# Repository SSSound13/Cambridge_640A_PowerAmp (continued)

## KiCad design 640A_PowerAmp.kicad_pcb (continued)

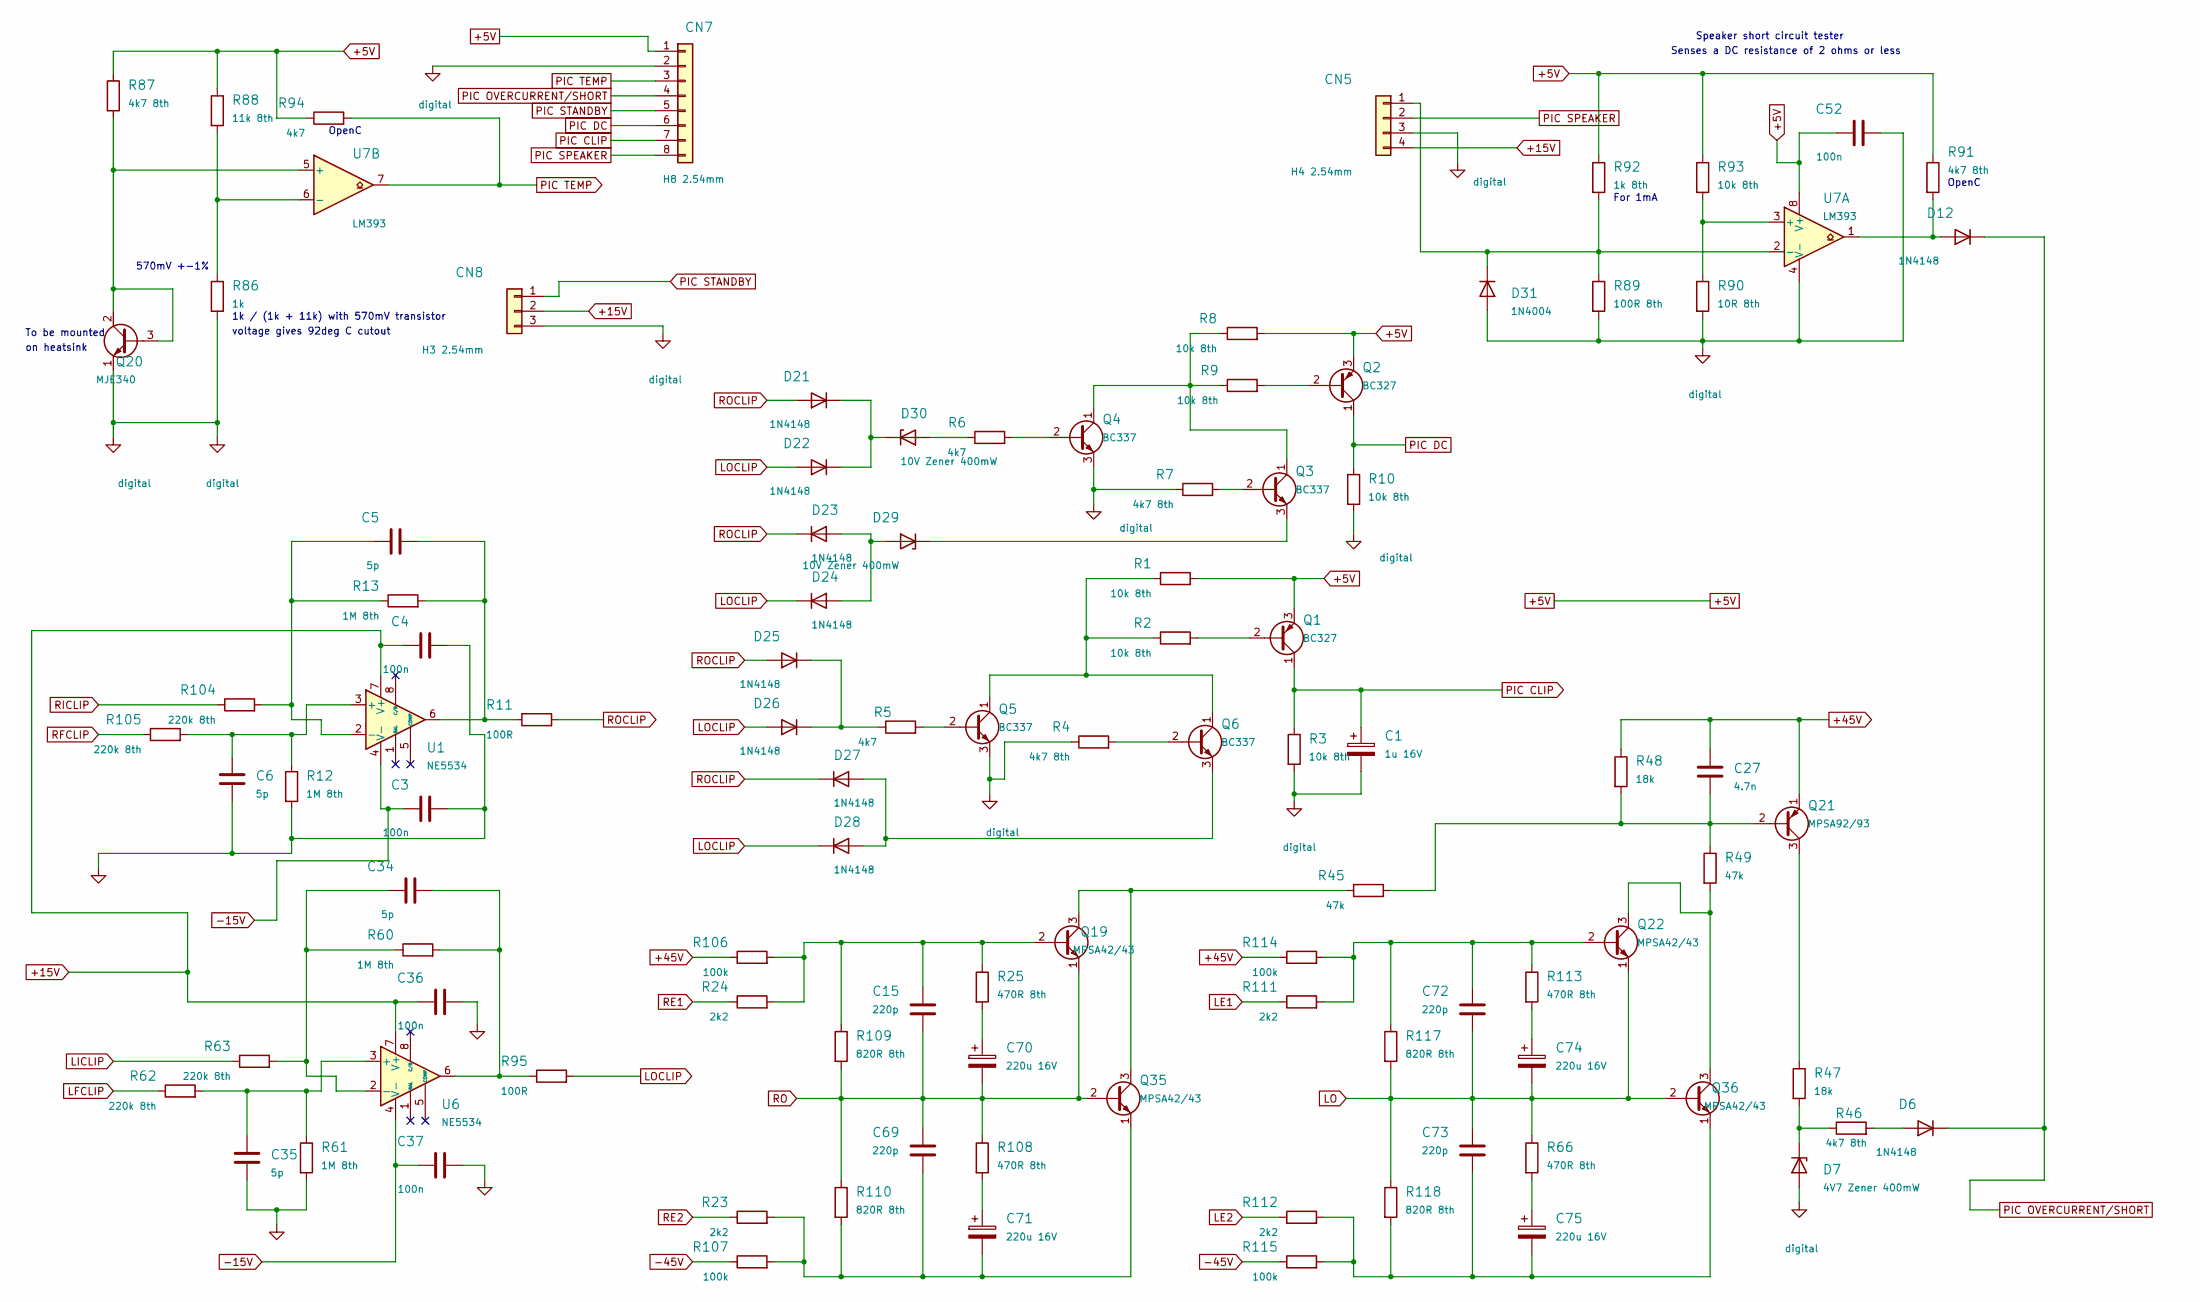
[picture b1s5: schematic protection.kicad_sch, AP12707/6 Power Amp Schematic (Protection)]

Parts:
C1: 1u 16V; CP_Radial_D5.0mm_P2.50mm
C3, C4, C36, C37, C52: 100n; C_Disc_D7.5mm_W2.5mm_P5.00mm
C5, C6, C34, C35: 5p; C_Disc_D5.0mm_W2.5mm_P5.00mm
C15, C69, C72, C73: 220p; C_Disc_D5.0mm_W2.5mm_P5.00mm
C27: 4.7n; C_Disc_D7.5mm_W2.5mm_P5.00mm
C70, C71, C74, C75: 220u 16V; CP_Radial_D5.0mm_P2.50mm
CN5: H4 2.54mm; JST_XH_B4B-XH-A_1x04_P2.50mm_Vertical
CN7: H8 2.54mm; JST_XH_B8B-XH-A_1x08_P2.50mm_Vertical
CN8: H3 2.54mm; JST_XH_B3B-XH-A_1x03_P2.50mm_Vertical
D6, D12, D21, D22, D23, D24, D25, D26, D27, D28: 1N4148; D_DO-35_SOD27_P7.62mm_Horizontal
D7: 4V7 Zener 400mW; D_DO-35_SOD27_P7.62mm_Horizontal
D29, D30: 10V Zener 400mW; D_DO-35_SOD27_P7.62mm_Horizontal
D31: 1N4004; D_DO-41_SOD81_P10.16mm_Horizontal
Q1, Q2: BC327; TO-92_Inline_Wide
Q3, Q4, Q5, Q6: BC337; TO-92_Inline_Wide
Q19, Q22, Q35, Q36: MPSA42/43; TO-92_Inline_Wide
Q20: MJE340; TO-126-3_Vertical
Q21: MPSA92/93; TO-92_Inline_Wide
R1, R2, R3, R8, R9, R10, R93: 10k 8th; R_Axial_DIN0204_L3.6mm_D1.6mm_P7.62mm_Horizontal
R4, R7, R87, R91: 4k7 8th; R_Axial_DIN0204_L3.6mm_D1.6mm_P7.62mm_Horizontal
R5, R6, R94: 4k7; R_Axial_DIN0207_L6.3mm_D2.5mm_P10.16mm_Horizontal
R11, R95: 100R; R_Axial_DIN0207_L6.3mm_D2.5mm_P10.16mm_Horizontal
R12, R13, R60, R61: 1M 8th; R_Axial_DIN0204_L3.6mm_D1.6mm_P7.62mm_Horizontal
R23, R24, R111, R112: 2k2; R_Axial_DIN0207_L6.3mm_D2.5mm_P10.16mm_Horizontal
R25, R66, R108, R113: 470R 8th; R_Axial_DIN0204_L3.6mm_D1.6mm_P7.62mm_Horizontal
R45, R49: 47k; R_Axial_DIN0207_L6.3mm_D2.5mm_P10.16mm_Horizontal
R46: 4k7 8th; R_Axial_DIN0207_L6.3mm_D2.5mm_P10.16mm_Horizontal
R47, R48: 18k; R_Axial_DIN0207_L6.3mm_D2.5mm_P10.16mm_Horizontal
R62, R63, R104, R105: 220k 8th; R_Axial_DIN0204_L3.6mm_D1.6mm_P7.62mm_Horizontal
R86: 1k; R_Axial_DIN0207_L6.3mm_D2.5mm_P10.16mm_Horizontal
R88: 11k 8th; R_Axial_DIN0204_L3.6mm_D1.6mm_P7.62mm_Horizontal
R89: 100R 8th; R_Axial_DIN0204_L3.6mm_D1.6mm_P7.62mm_Horizontal
R90: 10R 8th; R_Axial_DIN0204_L3.6mm_D1.6mm_P7.62mm_Horizontal
R92: 1k 8th; R_Axial_DIN0204_L3.6mm_D1.6mm_P7.62mm_Horizontal
R106, R107, R114, R115: 100k; R_Axial_DIN0207_L6.3mm_D2.5mm_P10.16mm_Horizontal
R109, R110, R117, R118: 820R 8th; R_Axial_DIN0204_L3.6mm_D1.6mm_P7.62mm_Horizontal
U1, U6: NE5534; DIP-8_W7.62mm
U7: LM393; DIP-8_W7.62mm

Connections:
+5V: C52.1, CN7.1, Q1.3 (E), Q2.3 (E), R1.2, R8.2, R87.1, R88.1, R91.1, R92.1, R93.1, R94.1, U7.8 (V+); also elsewhere on the board
+15V: C4.1, C36.1, CN5.4, CN8.2, U1.7 (V+), U6.7 (V+); also elsewhere on the board
+45V: C27.1, Q21.1 (E), R48.1, R106.1, R114.1; also elsewhere on the board
-15V: C3.1, C37.1, U1.4 (V-), U6.4 (V-); also elsewhere on the board
-45V: R107.1, R115.1; also elsewhere on the board
GND: C3.2, C4.2, C6.2, C35.2, C36.2, C37.2, R12.2, R61.2; also elsewhere on the board
LE1: R111.1; also elsewhere on the board
LE2: R112.1; also elsewhere on the board
LFCLIP: R62.1; also elsewhere on the board
LICLIP: R63.1; also elsewhere on the board
LO: C72.2, C73.1, C74.2, Q22.1 (E), Q36.2 (B), R66.1, R117.2, R118.1; also elsewhere on the board
LOCLIP: D22.2 (A), D24.1 (K), D26.2 (A), D28.1 (K), R95.2
unnamed: C5.2, R11.1, R13.2, U1.6
unnamed: C34.2, R60.2, R95.1, U6.6
unnamed: C70.1, R25.2
unnamed: C71.1, R108.2
unnamed: C74.1, R113.2
unnamed: C75.1, R66.2
unnamed: CN5.1, D31.1 (K), R89.1, R92.2, U7.2 (-)
unnamed: D6.2 (A), R46.2
unnamed: D7.1 (K), R46.1, R47.2
unnamed: D12.2 (A), R91.2, U7.1
unnamed: D21.1 (K), D22.1 (K), D30.1 (K)
unnamed: D23.2 (A), D24.2 (A), D29.2 (A)
unnamed: D25.1 (K), D26.1 (K), R5.1
unnamed: D27.2 (A), D28.2 (A), Q6.3 (E)
unnamed: D29.1 (K), Q3.3 (E)
unnamed: D30.2 (A), R6.1
unnamed: Q1.2 (B), R2.2
unnamed: Q2.2 (B), R9.2
unnamed: Q3.2 (B), R7.2
unnamed: Q3.1 (C), Q4.1 (C), R8.1, R9.1
unnamed: Q4.2 (B), R6.2
unnamed: Q5.2 (B), R5.2
unnamed: Q5.1 (C), Q6.1 (C), R1.1, R2.1
unnamed: Q6.2 (B), R4.2
unnamed: C15.1, Q19.2 (B), R24.2, R25.1, R106.2, R109.1
unnamed: Q19.3 (C), Q35.3 (C), R45.1
unnamed: Q20.2 (C), Q20.3 (B), R87.2, U7.5 (+)
unnamed: C27.2, Q21.2 (B), R45.2, R48.2, R49.1
unnamed: Q21.3 (C), R47.1
unnamed: C72.1, Q22.2 (B), R111.2, R113.1, R114.2, R117.1
unnamed: Q22.3 (C), Q36.3 (C), R49.2
unnamed: C69.2, C71.2, Q35.1 (E), R23.2, R107.2, R110.2
unnamed: C73.2, C75.2, Q36.1 (E), R112.2, R115.2, R118.2
unnamed: C6.1, R12.1, R105.2, U1.3 (+)
unnamed: C5.1, R13.1, R104.2, U1.2 (-)
unnamed: C35.1, R61.1, R62.2, U6.3 (+)
unnamed: C34.1, R60.1, R63.2, U6.2 (-)
unnamed: R90.1, R93.2, U7.3 (+)
unnamed: R86.1, R88.2, U7.6 (-)
PIC CLIP: C1.1, CN7.7, Q1.1 (C), R3.1
PIC DC: CN7.6, Q2.1 (C), R10.1
PIC OVERCURRENT/SHORT: CN7.4, D6.1 (K), D12.1 (K)
PIC SPEAKER: CN5.2, CN7.8
PIC STANDBY: CN7.5, CN8.1
PIC TEMP: CN7.3, R94.2, U7.7
RE1: R24.1; also elsewhere on the board
RE2: R23.1; also elsewhere on the board
RFCLIP: R105.1; also elsewhere on the board
RICLIP: R104.1; also elsewhere on the board
RO: C15.2, C69.1, C70.2, Q19.1 (E), Q35.2 (B), R108.1, R109.2, R110.1; also elsewhere on the board
ROCLIP: D21.2 (A), D23.1 (K), D25.2 (A), D27.1 (K), R11.2
digital: C1.2, C52.2, CN5.3, CN7.2, CN8.3, D7.2 (A), D31.2 (A), Q4.3 (E), Q5.3 (E), Q20.1 (E), R3.2, R4.1, R7.1, R10.2, R86.2, R89.2, R90.2, U7.4 (V-); also elsewhere on the board

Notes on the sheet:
570mV +-1%
For 1mA
OpenC
Senses a DC resistance of 2 ohms or less
To be mounted
Speaker short circuit tester
on heatsink
voltage gives 92deg C cutout
1k / (1k + 11k) with 570mV transistor

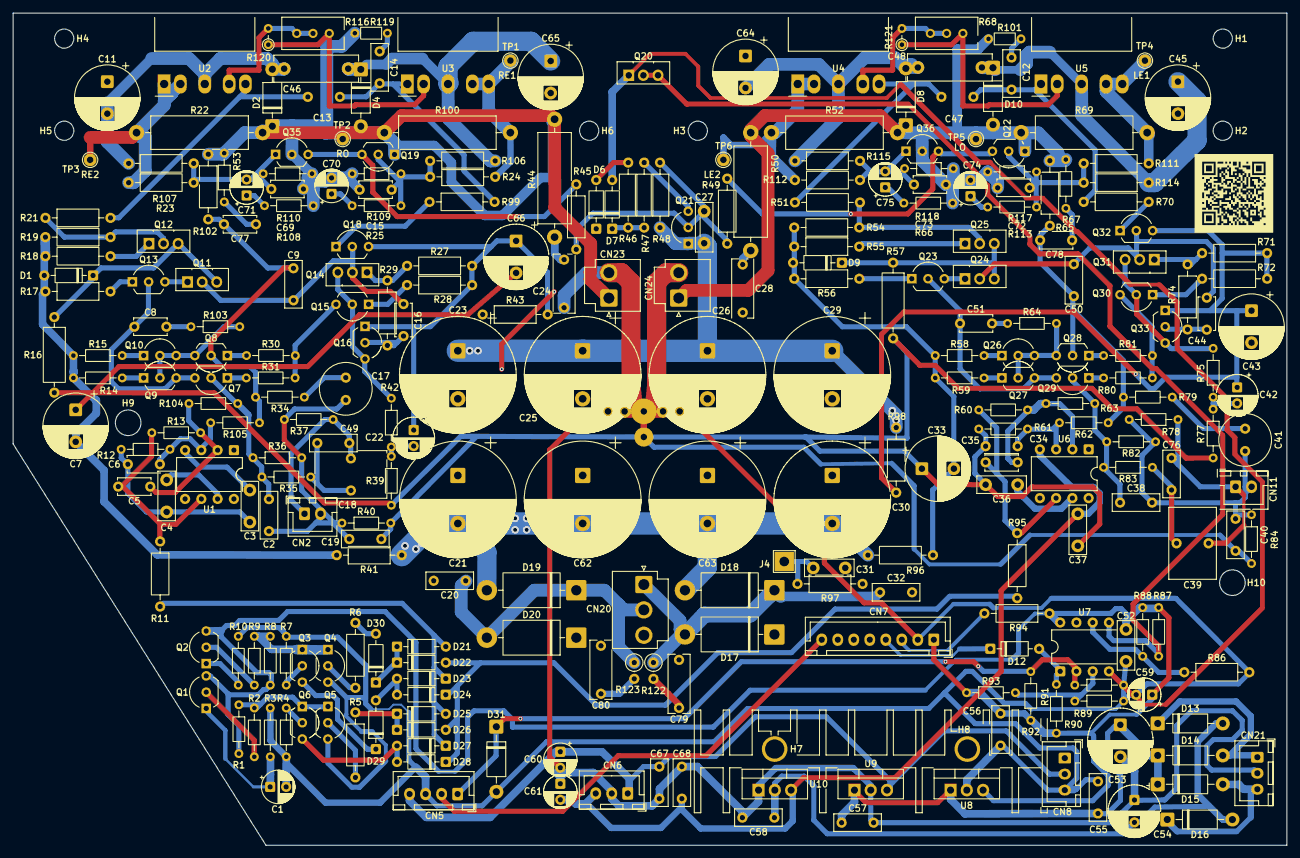
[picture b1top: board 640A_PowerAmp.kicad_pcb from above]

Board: 4 copper layers, 198.9 x 130.0 mm, 296 parts (0 on the bottom side), 141 nets.

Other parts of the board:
H1, H2, H3, H4, H5, H6: bracket fixing, 3.0 mm NPTH; MountingHole_NPTH_3.0mm
H7: heatsink pin, 3.0 mm PTH; MountingHole_PTH_3.0mm_Pad4.0mm
H8: heatsink pin, 3.0 mm PTH; no separate digital tra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; MountingHole_PTH_3.0mm_Pad4.0mm
H9, H10: standoff, 4.0 mm NPTH; MountingHole_NPTH_4.0mm

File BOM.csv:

Группа;Кол-во;Обозначения;Номинал;Корпус;Производитель и партномер;Новое/заменено;Не устанавливать;Код ЧИП и ДИП;Примечание
Резисторы;11;R1, R2, R3, R8, R9, R10, R39, R42, R75, R77, R93;10k, 0,125 Вт;DIN0204, шаг 7,62;;;;;
Резисторы;6;R4, R7, R35, R83, R87, R91;4k7, 0,125 Вт;DIN0204, шаг 7,62;;;;;
Резисторы;3;R5, R6, R94;4k7;DIN0207, шаг 10,16;;;;;
Резисторы;8;R11, R17, R21, R51, R56, R70, R95, R99;100R;DIN0207, шаг 10,16;;;;;
Резисторы;4;R12, R13, R60, R61;1M, 0,125 Вт;DIN0204, шаг 7,62;;;;;
Резисторы;4;R14, R15, R58, R59;47R, 0,125 Вт;DIN0204, шаг 7,62;;;;;
Резисторы;2;R16, R57;8k2 0,66 Вт;DIN0309, шаг 11,81;;;;;
Резисторы;5;R18, R29, R55, R74, R86;1k;DIN0207, шаг 10,16;;;;;
Резисторы;4;R19, R47, R48, R54;18k;DIN0207, шаг 10,16;;;;;
Резисторы;4;R22, R52, R69, R100;0.22R 3 Вт;DIN0516, шаг 19,69;;;;;
Резисторы;4;R23, R24, R111, R112;2k2;DIN0207, шаг 10,16;;;;;
Резисторы;4;R25, R66, R108, R113;470R, 0,125 Вт;DIN0204, шаг 7,62;;;;;
Резисторы;4;R27, R28, R71, R72;150R;DIN0207, шаг 10,16;;;;;
Резисторы;5;R30, R31, R80, R81, R89;100R, 0,125 Вт;DIN0204, шаг 7,62;;;;;
Резисторы;3;R34, R79, R92;1k, 0,125 Вт;DIN0204, шаг 7,62;;;;;
Резисторы;2;R36, R82;33k, 0,125 Вт;DIN0204, шаг 7,62;;;;;
Резисторы;2;R37, R78;330k, 0,125 Вт;DIN0204, шаг 7,62;;;;;
Резисторы;3;R40, R84, R90;10R, 0,125 Вт;DIN0204, шаг 7,62;;;;;
Резисторы;4;R41, R43, R96, R98;150R 0,5 Вт fusible;DIN0207, шаг 10,16;TE Connectivity (Neohm) FRN50J150R/S;да;;8003870514;
Резисторы;2;R44, R50;4R7 3 Вт wirewound;DIN0516, шаг 18,42;Vishay AC03000004708JAC00;да;;8017149996;"ставить на выводах ~3 мм над платой (иначе касается R45); можно родные со старой платы"
Резисторы;2;R45, R49;47k;DIN0207, шаг 10,16;;;;;
Резисторы;1;R46;4k7, 0,125 Вт;DIN0207, шаг 10,16;;;;;
Резисторы;1;R53;150R, 0,125 Вт;DIN0204, шаг 7,62;;;;;
Резисторы;4;R62, R63, R104, R105;220k, 0,125 Вт;DIN0204, шаг 7,62;;;;;
Резисторы;3;R64, R67, R103;150R;DIN0204, шаг 7,62;;;;;
Резисторы;2;R65, R102;33k;DIN0207, шаг 10,16;;;;;
Резисторы;2;R68, R116;47R;Bourns 3296W;;;;;подстроечник тока покоя
Резисторы;1;R88;11k, 0,125 Вт;DIN0204, шаг 7,62;;;;;
Резисторы;1;R97;47R;DIN0207, шаг 10,16;;;;;
Резисторы;2;R101, R119;47R, 0,125 Вт;DIN0204, шаг 5,08;;;;;
Резисторы;4;R106, R107, R114, R115;100k;DIN0207, шаг 10,16;;;;;
Резисторы;4;R109, R110, R117, R118;820R, 0,125 Вт;DIN0204, шаг 7,62;;;;;
Резисторы;2;R120, R121;100R 1%;DIN0204 вертикально;MF-25 0.25W 100R 1%;да;;47324;
Резисторы;2;R122, R123;47R 0,5 Вт MO;DIN0207 вертикально;MO-50 0.5W 47R 5%;да;;9000040018;номинал подобрать по звону вторички
Конденсаторы;1;C1;1u 16V;радиальный Ø5, шаг 2,5;;;;;
Конденсаторы;2;C2, C38;100p poly;7,2×2,5 мм, шаг 5;;;;;
Конденсаторы;6;C3, C4, C31, C36, C37, C52;100n;диск Ø7,5, шаг 5;;;;;
Конденсаторы;4;C5, C6, C34, C35;5p;диск Ø5, шаг 5;;;;;
Конденсаторы;8;C7, C11, C33, C43, C45, C64, C65, C66;220u 50V;радиальный Ø10, шаг 5;;;;;C7/C33/C43/C66 желательно на 63 В
Конденсаторы;2;C8, C51;470p;диск Ø5, шаг 5;;;;;
Конденсаторы;2;C9, C50;33p;7,2×2,5 мм, шаг 5;;;;;
Конденсаторы;2;C12, C14;15n poly;7,2×2,5 мм, шаг 5;;;;;
Конденсаторы;2;C13, C47;10u NP 16V;радиальный Ø5, шаг 5;;;;;
Конденсаторы;4;C15, C69, C72, C73;220p;диск Ø5, шаг 5;;;;;
Конденсаторы;2;C16, C44;5p;диск Ø5, шаг 5;;;да;;**не устанавливать** (DNP), место под коррекцию на случай возбуждения
Конденсаторы;2;C17, C41;220u NP 10V (D8);радиальный Ø8, шаг 3,5;Panasonic ECE-A1AN221U;да;;8072492276;
Конденсаторы;2;C18, C39;2u2 100V film (MKS2);7,2×11 мм, шаг 5;WIMA MKS2D042201N00KO00 (MKS2-2.2U/100-R);да;;9000788913;
Конденсаторы;10;C19, C20, C32, C40, C55, C56, C57, C58, C67, C68;47n poly;7,2×2,5 мм, шаг 5;;;;;
Конденсаторы;8;C21, C23, C25, C26, C29, C30, C62, C63;2200uF;радиальный Ø18, шаг 7,5;;;;;
Конденсаторы;2;C22, C42;47u 50V;радиальный Ø6,3, шаг 2,5;;;;;C22 брать Ø5 мм — место тесное
Конденсаторы;4;C24, C28, C79, C80;100n 250V MKT;9×3,2 мм, шаг 7,5;TDK (EPCOS) B32560J3104K000;да;;8002013680;
Конденсаторы;1;C27;4.7n;диск Ø7,5, шаг 5;;;;;
Конденсаторы;2;C46, C48;100n 160V Poly;13×4 мм, шаг 10;;;;;
Конденсаторы;2;C49, C76;2.2n PPE Bypass (640A only);7,2×2,5 мм, шаг 5;;;;;
Конденсаторы;1;C53;470u 35V;радиальный Ø10, шаг 5;;;;;
Конденсаторы;1;C54;100u 35V;радиальный Ø8, шаг 3,5;;;;;
Конденсаторы;1;C59;47u 16V;радиальный Ø5, шаг 2,5;;;;;
Конденсаторы;2;C60, C61;100u 16V;радиальный Ø5, шаг 2,5;;;;;
Конденсаторы;4;C70, C71, C74, C75;220u 16V;радиальный Ø5, шаг 2,5;;;;;
Конденсаторы;2;C77, C78;22p;диск Ø5, шаг 5;;;;;
Диоды;2;D1, D9;ZEN 3V3;DO 35, шаг 7,62;;;;;
Диоды;4;D2, D4, D8, D10;1N4004;DO 41, шаг 8,89;;;;;
Диоды;10;D6, D12, D21, D22, D23, D24, D25, D26, D27, D28;1N4148;DO 35, шаг 7,62;;;;;
Диоды;1;D7;4V7 Zener 400mW;DO 35, шаг 7,62;;;;;
Диоды;5;D13, D14, D15, D16, D31;1N4004;DO 41, шаг 10,16;;;;;
Диоды;4;D17, D18, D19, D20;BY550-400;DO 201AD, шаг 13,97;Diotec BY550-400;да;;8026566344;
Диоды;2;D29, D30;10V Zener 400mW;DO 35, шаг 7,62;;;;;
Транзисторы;2;Q1, Q2;BC327;TO-92;;;;;
Транзисторы;4;Q3, Q4, Q5, Q6;BC337;TO-92;;;;;
Транзисторы;9;Q7, Q8, Q15, Q16, Q21, Q28, Q29, Q30, Q33;MPSA92/93;TO-92;;;;;
Транзисторы;10;Q9, Q10, Q18, Q19, Q22, Q26, Q27, Q32, Q35, Q36;MPSA42/43;TO-92;;;;;
Транзисторы;5;Q11, Q12, Q20, Q24, Q25;MJE340;TO-126;;;;;
Транзисторы;2;Q13, Q23;MPSA13;TO-92;;;;;
Транзисторы;2;Q14, Q31;MJE350;TO-126;;;;;
Микросхемы и модули;2;U1, U6;NE5534;DIP-8;;;;;
Микросхемы и модули;2;U2, U4;SAP15P;TO-3P-5 (лёжа на радиаторе);;;;;Sanken, снят с производства — переставить со старой платы
Микросхемы и модули;2;U3, U5;SAP15N;TO-3P-5 (лёжа на радиаторе);;;;;Sanken, снят с производства — переставить со старой платы
Микросхемы и модули;1;U7;LM393;DIP-8;;;;;
Микросхемы и модули;1;U8;7805;"TO-220 стандартный KiCad; шаг 2,54 мм, отверстия 1,1 мм";;;;;"целый радиатор AP12106/1; без изолятора, с термопастой. На изготовленной v2 Ø1,0 мм; посадка использованного TO-220 проверена при сборке, рассверливание не требуется"
Микросхемы и модули;1;U9;7815;TO-220;;;;;на общем радиаторе с изоляционным комплектом и термопастой (мануал стр.25)
Микросхемы и модули;1;U10;7915;TO-220;;;;;на общем радиаторе с изоляционным комплектом и термопастой (мануал стр.25)
Разъёмы;2;CN2, CN11;H2 2.54mm;JST XH, шаг 2,5;;;;;
Разъёмы;1;CN5;H4 2.54mm;JST XH, шаг 2,5;;;;;
Разъёмы;2;CN6, CN8;H3 2.54mm;JST XH, шаг 2,5;;;;;
Разъёмы;1;CN7;H8 2.54mm;JST XH, шаг 2,5;;;;;
Разъёмы;1;CN20;B3P-VH;JST VH, шаг 3,96;JST B3P-VH;да;;222965310;
Разъёмы;1;CN21;B3B-XH-A;JST XH, шаг 2,5;JST B3B-XH-A;да;;203820430;
Разъёмы;2;CN23, CN24;B2P-VH;JST VH, шаг 3,96;JST B2P-VH;да;;56245612;
Прочее;1;J4;CHASSIS;площадка 3×3 мм;;;;;клемма связи PGND с корпусом (провод на стойку), деталь не нужна
Прочее;6;TP1–TP6;RE1, RO, RE2 / LE1, LO, LE2;площадка Ø2 мм;;да;;;контрольные точки для настройки тока покоя, деталь не нужна
